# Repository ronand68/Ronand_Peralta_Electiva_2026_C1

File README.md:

Repositorio de la clase Electiva

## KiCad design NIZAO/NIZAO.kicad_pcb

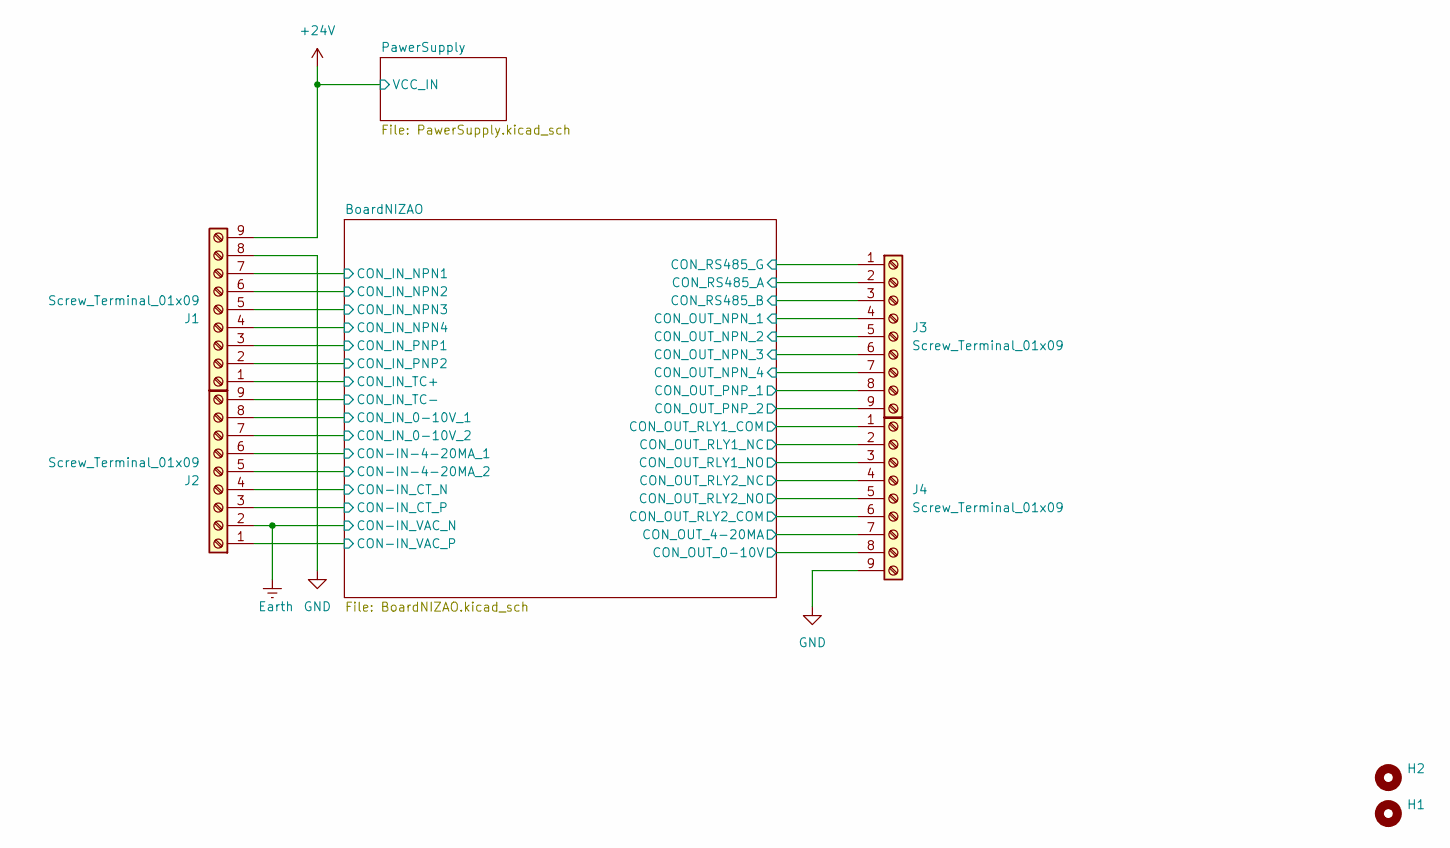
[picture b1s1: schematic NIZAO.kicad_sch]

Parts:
H1, H2: MountingHole; MountingHole_3.2mm_M3
J1, J2, J3, J4: Screw_Terminal_01x09; TerminalBlock_Phoenix_PT-1,5-9-5.0-H_1x09_P5.00mm_Horizontal

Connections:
+24V: J1.9; also elsewhere on the board
/BoardNIZAO/CON-IN-4-20MA_1: J2.6; also elsewhere on the board
/BoardNIZAO/CON-IN-4-20MA_2: J2.5; also elsewhere on the board
/BoardNIZAO/CON-IN_CT_N: J2.4; also elsewhere on the board
/BoardNIZAO/CON-IN_CT_P: J2.3; also elsewhere on the board
/BoardNIZAO/CON-IN_VAC_P: J2.1; also elsewhere on the board
/BoardNIZAO/CON_IN_0-10V_1: J2.8; also elsewhere on the board
/BoardNIZAO/CON_IN_0-10V_2: J2.7; also elsewhere on the board
/BoardNIZAO/CON_IN_NPN1: J1.7; also elsewhere on the board
/BoardNIZAO/CON_IN_NPN2: J1.6; also elsewhere on the board
/BoardNIZAO/CON_IN_NPN3: J1.5; also elsewhere on the board
/BoardNIZAO/CON_IN_NPN4: J1.4; also elsewhere on the board
/BoardNIZAO/CON_IN_PNP1: J1.3; also elsewhere on the board
/BoardNIZAO/CON_IN_PNP2: J1.2; also elsewhere on the board
/BoardNIZAO/CON_IN_TC+: J1.1; also elsewhere on the board
/BoardNIZAO/CON_IN_TC-: J2.9; also elsewhere on the board
/BoardNIZAO/CON_OUT_0-10V: J4.8; also elsewhere on the board
/BoardNIZAO/CON_OUT_4-20MA: J4.7; also elsewhere on the board
/BoardNIZAO/CON_OUT_NPN_1: J3.4; also elsewhere on the board
/BoardNIZAO/CON_OUT_NPN_2: J3.5; also elsewhere on the board
/BoardNIZAO/CON_OUT_NPN_3: J3.6; also elsewhere on the board
/BoardNIZAO/CON_OUT_NPN_4: J3.7; also elsewhere on the board
/BoardNIZAO/CON_OUT_PNP_1: J3.8; also elsewhere on the board
/BoardNIZAO/CON_OUT_PNP_2: J3.9; also elsewhere on the board
/BoardNIZAO/CON_OUT_RLY1_COM: J4.1; also elsewhere on the board
/BoardNIZAO/CON_OUT_RLY1_NC: J4.2; also elsewhere on the board
/BoardNIZAO/CON_OUT_RLY1_NO: J4.3; also elsewhere on the board
/BoardNIZAO/CON_OUT_RLY2_COM: J4.6; also elsewhere on the board
/BoardNIZAO/CON_OUT_RLY2_NC: J4.4; also elsewhere on the board
/BoardNIZAO/CON_OUT_RLY2_NO: J4.5; also elsewhere on the board
/BoardNIZAO/CON_RS485_A: J3.2; also elsewhere on the board
/BoardNIZAO/CON_RS485_B: J3.3; also elsewhere on the board
/BoardNIZAO/CON_RS485_G: J3.1; also elsewhere on the board
Earth: J2.2; also elsewhere on the board
GND: J1.8, J4.9; also elsewhere on the board

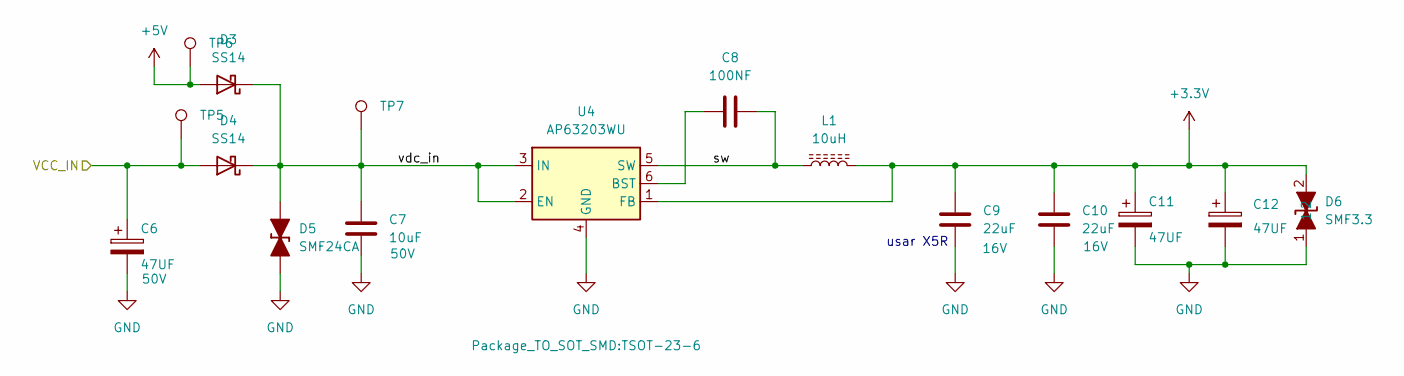
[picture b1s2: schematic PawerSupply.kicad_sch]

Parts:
C6: 47UF; CP_Elec_6.3x7.7; Part Number C2887275; LCSC Part C2887275
C7: 10uF; C_0805_2012Metric; Part Number GRM21BR61H106KE43L; LCSC Part C440198
C8: 100NF; C_0805_2012Metric; Part Number CC0805KRX7R9BB104; LCSC Part C49678
C9, C10: 22uF; C_0805_2012Metric; Part Number CL21A226MOQNNNE; LCSC Part C98190
C11, C12: 47UF; CP_Elec_6.3x7.7; Part Number UUD1C470MCL1GS
D3, D4: SS14; D_SMA
D5: SMF24CA; D_SOD-123F
D6: SMF3.3; SMF3_3CA_C6165153; Manufacturer Part SMF3.3CA; LCSC C6165153
L1: 10uH; L_APV_APH0630; Part Number SL0630-100M; LCSC Part C22463823
TP5, TP6, TP7: TestPoint_Hole1; TestPoint_THTPad_D1.5mm_Drill0.7mm
U4: AP63203WU; TSOT-23-6

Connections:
+3.3V: C9.1, C10.1, C11.1, C12.1, D6.2, L1.2, U4.1 (FB); also elsewhere on the board
+5V: D3.2 (A), TP6.1 (1_1); also elsewhere on the board
+24V: C6.1, D4.2 (A), TP5.1; also elsewhere on the board
/PawerSupply/sw: C8.2, L1.1, U4.5 (SW)
/PawerSupply/vdc_in: C7.1, D3.1 (K), D4.1 (K), D5.2 (A), TP7.1 (1_1), U4.2 (EN), U4.3 (IN)
GND: C6.2, C7.2, C9.2, C10.2, C11.2, C12.2, D5.1 (K), D6.1, U4.4 (GND); also elsewhere on the board
unnamed: C8.1, U4.6 (BST)

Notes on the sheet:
usar X5R

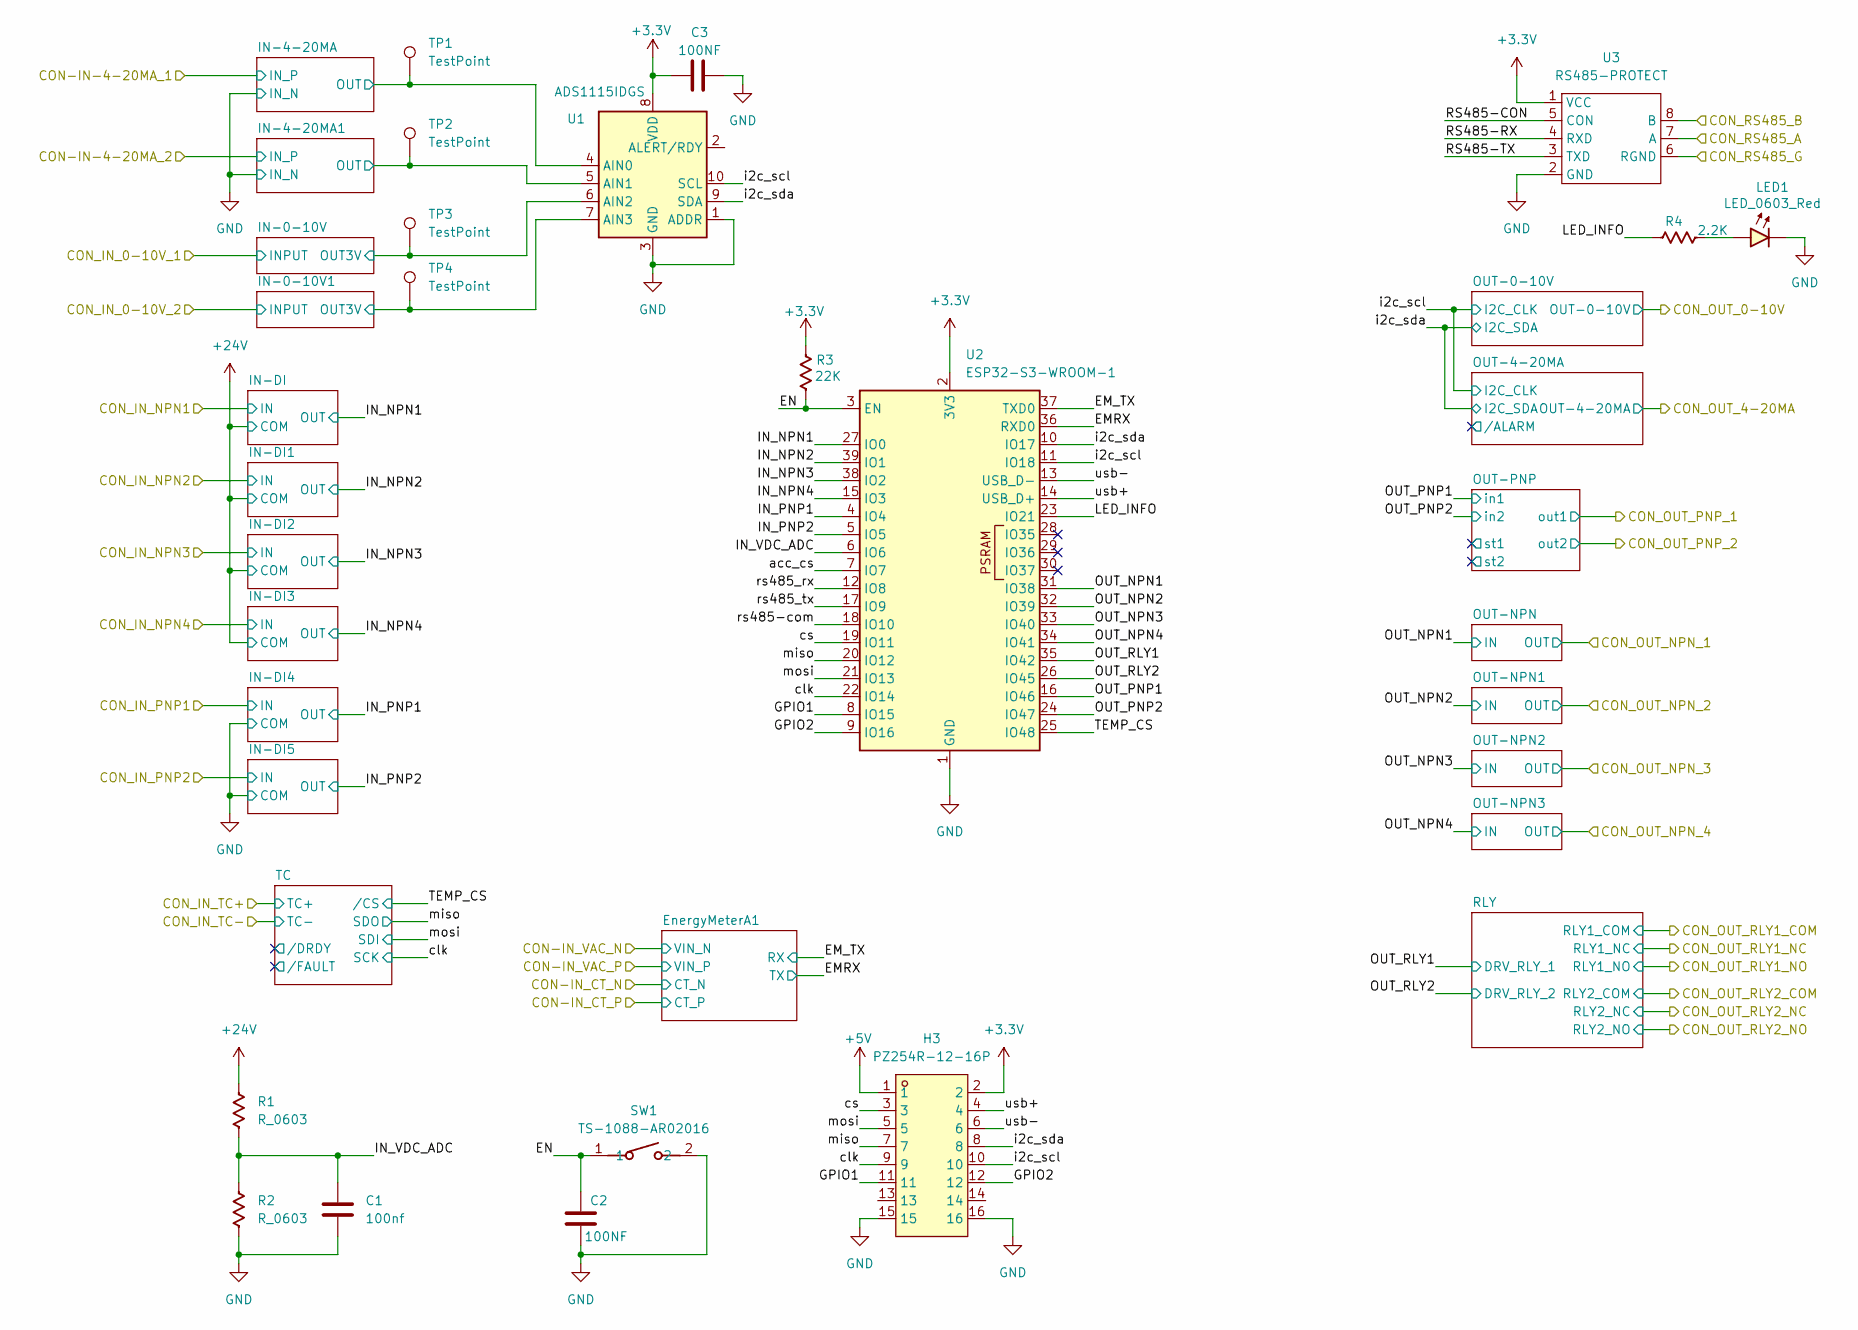
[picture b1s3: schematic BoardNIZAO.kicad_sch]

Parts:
C1: 100nf; C_0603_1608Metric
C2, C3: 100NF; C_0603_1608Metric
H3: PZ254R-12-16P; HDR-TH_16P-P2.54-H-M-R2-C8-S2.54; LCSC Part C492436
LED1: LED_0603_Red; LED_0603_1608Metric
R1, R2: R_0603; R_0603_1608Metric
R3: 22K; R_0603_1608Metric
R4: 2.2K; R_0603_1608Metric
SW1: TS-1088-AR02016; Manufacturer Part TS-1088-AR02016; LCSC C720477
TP1, TP2, TP3, TP4: TestPoint; TestPoint_THTPad_D1.5mm_Drill0.7mm
U1: ADS1115IDGS; TSSOP-10_3x3mm_P0.5mm
U2: ESP32-S3-WROOM-1; ESP32-S3-WROOM-1U
U3: RS485-PROTECT; RS-485-PROTECT; Part Number RS-485-PROTECT

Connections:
+3.3V: C3.1, H3.2, R3.2, U1.8 (VDD), U2.2 (3V3), U3.1 (VCC); also elsewhere on the board
+5V: H3.1; also elsewhere on the board
+24V: R1.1; also elsewhere on the board
/BoardNIZAO/CON_RS485_A: U3.7 (A); also elsewhere on the board
/BoardNIZAO/CON_RS485_B: U3.8 (B); also elsewhere on the board
/BoardNIZAO/CON_RS485_G: U3.6 (RGND); also elsewhere on the board
/BoardNIZAO/EMRX: U2.36 (RXD0); also elsewhere on the board
/BoardNIZAO/EM_TX: U2.37 (TXD0); also elsewhere on the board
/BoardNIZAO/EN: C2.2, R3.1, SW1.1, U2.3 (EN)
/BoardNIZAO/GPIO1: H3.11, U2.8 (IO15)
/BoardNIZAO/GPIO2: H3.12, U2.9 (IO16)
/BoardNIZAO/IN-0-10V1/OUT3V: TP4.1 (1_1), U1.7 (AIN3); also elsewhere on the board
/BoardNIZAO/IN-0-10V/OUT3V: TP3.1 (1_1), U1.6 (AIN2); also elsewhere on the board
/BoardNIZAO/IN-4-20MA1/OUT: TP2.1 (1_1), U1.5 (AIN1); also elsewhere on the board
/BoardNIZAO/IN-4-20MA/OUT: TP1.1 (1_1), U1.4 (AIN0); also elsewhere on the board
/BoardNIZAO/IN_NPN1: U2.27 (IO0); also elsewhere on the board
/BoardNIZAO/IN_NPN2: U2.39 (IO1); also elsewhere on the board
/BoardNIZAO/IN_NPN3: U2.38 (IO2); also elsewhere on the board
/BoardNIZAO/IN_NPN4: U2.15 (IO3); also elsewhere on the board
/BoardNIZAO/IN_PNP1: U2.4 (IO4); also elsewhere on the board
/BoardNIZAO/IN_PNP2: U2.5 (IO5); also elsewhere on the board
/BoardNIZAO/IN_VDC_ADC: C1.1, R1.2, R2.1, U2.6 (IO6)
/BoardNIZAO/LED_INFO: R4.2, U2.23 (IO21)
/BoardNIZAO/OUT_NPN1: U2.31 (IO38); also elsewhere on the board
/BoardNIZAO/OUT_NPN2: U2.32 (IO39); also elsewhere on the board
/BoardNIZAO/OUT_NPN3: U2.33 (IO40); also elsewhere on the board
/BoardNIZAO/OUT_NPN4: U2.34 (IO41); also elsewhere on the board
/BoardNIZAO/OUT_PNP1: U2.16 (IO46); also elsewhere on the board
/BoardNIZAO/OUT_PNP2: U2.24 (IO47); also elsewhere on the board
/BoardNIZAO/OUT_RLY1: U2.35 (IO42); also elsewhere on the board
/BoardNIZAO/OUT_RLY2: U2.26 (IO45); also elsewhere on the board
/BoardNIZAO/RS485-CON: U3.5 (CON)
/BoardNIZAO/RS485-RX: U3.4 (RXD)
/BoardNIZAO/RS485-TX: U3.3 (TXD)
/BoardNIZAO/TEMP_CS: U2.25 (IO48); also elsewhere on the board
/BoardNIZAO/acc_cs: U2.7 (IO7)
/BoardNIZAO/clk: H3.9, U2.22 (IO14); also elsewhere on the board
/BoardNIZAO/cs: H3.3, U2.19 (IO11)
/BoardNIZAO/i2c_scl: H3.10, U1.10 (SCL), U2.11 (IO18); also elsewhere on the board
/BoardNIZAO/i2c_sda: H3.8, U1.9 (SDA), U2.10 (IO17); also elsewhere on the board
/BoardNIZAO/miso: H3.7, U2.20 (IO12); also elsewhere on the board
/BoardNIZAO/mosi: H3.5, U2.21 (IO13); also elsewhere on the board
/BoardNIZAO/rs485-com: U2.18 (IO10)
/BoardNIZAO/rs485_rx: U2.12 (IO8)
/BoardNIZAO/rs485_tx: U2.17 (IO9)
/BoardNIZAO/usb+: H3.4, U2.14 (USB_D+)
/BoardNIZAO/usb-: H3.6, U2.13 (USB_D-)
GND: C1.2, C2.1, C3.2, H3.15, H3.16, LED1.1 (K), R2.2, SW1.2, U1.1 (ADDR), U1.3 (GND), U2.1 (GND), U2.40 (GND), U2.41 (GND), U3.2 (GND); also elsewhere on the board
unnamed: LED1.2 (A), R4.1

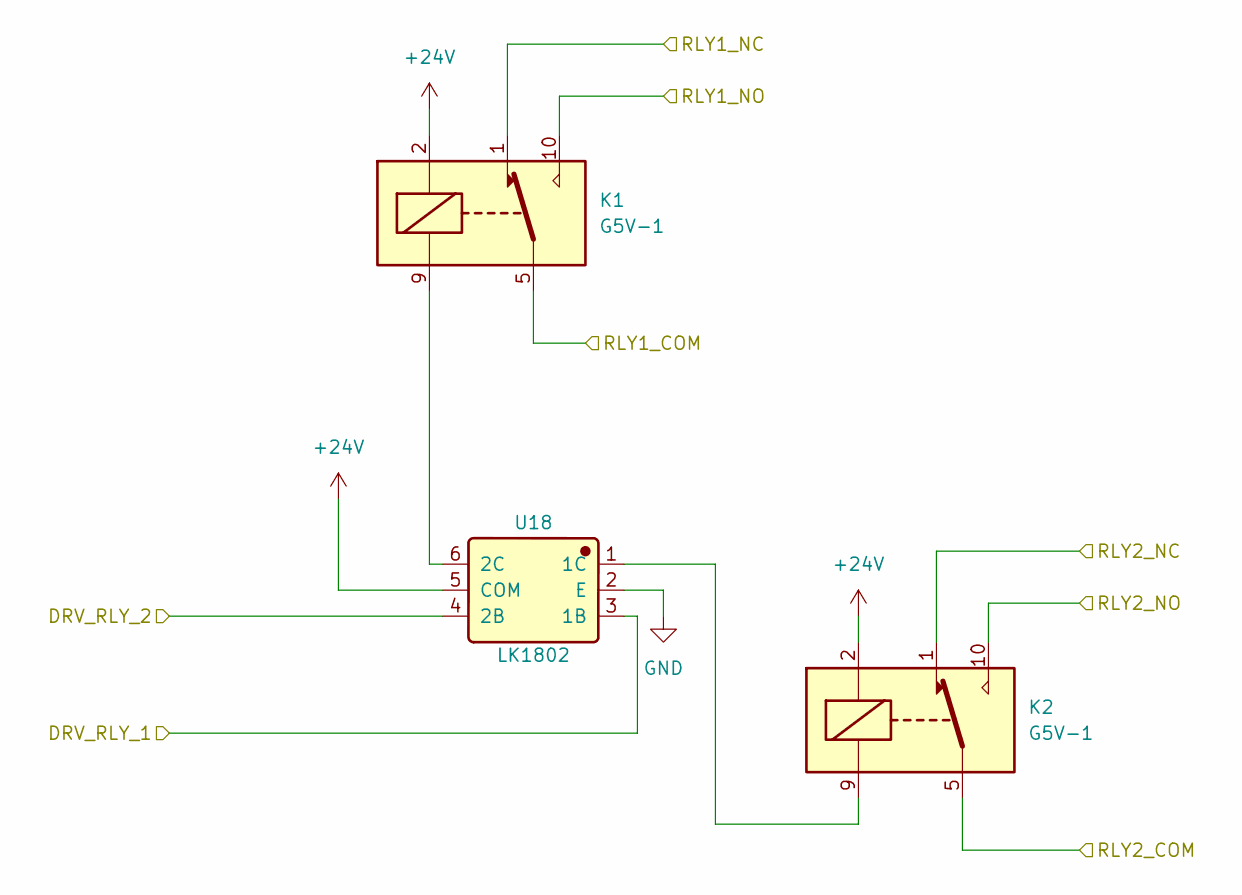
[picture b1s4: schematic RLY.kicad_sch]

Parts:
K1, K2: G5V-1; Relay_SPDT_Omron_G5V-1
U18: LK1802; Manufacturer Part LK1802; LCSC Part C2984831

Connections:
+24V: K1.2, K2.2, U18.5 (COM); also elsewhere on the board
/BoardNIZAO/CON_OUT_RLY1_COM: K1.5, K1.6; also elsewhere on the board
/BoardNIZAO/CON_OUT_RLY1_NC: K1.1; also elsewhere on the board
/BoardNIZAO/CON_OUT_RLY1_NO: K1.10; also elsewhere on the board
/BoardNIZAO/CON_OUT_RLY2_COM: K2.5, K2.6; also elsewhere on the board
/BoardNIZAO/CON_OUT_RLY2_NC: K2.1; also elsewhere on the board
/BoardNIZAO/CON_OUT_RLY2_NO: K2.10; also elsewhere on the board
/BoardNIZAO/OUT_RLY1: U18.3 (1B); also elsewhere on the board
/BoardNIZAO/OUT_RLY2: U18.4 (2B); also elsewhere on the board
GND: U18.2 (E); also elsewhere on the board
unnamed: K2.9, U18.1 (1C)
unnamed: K1.9, U18.6 (2C)

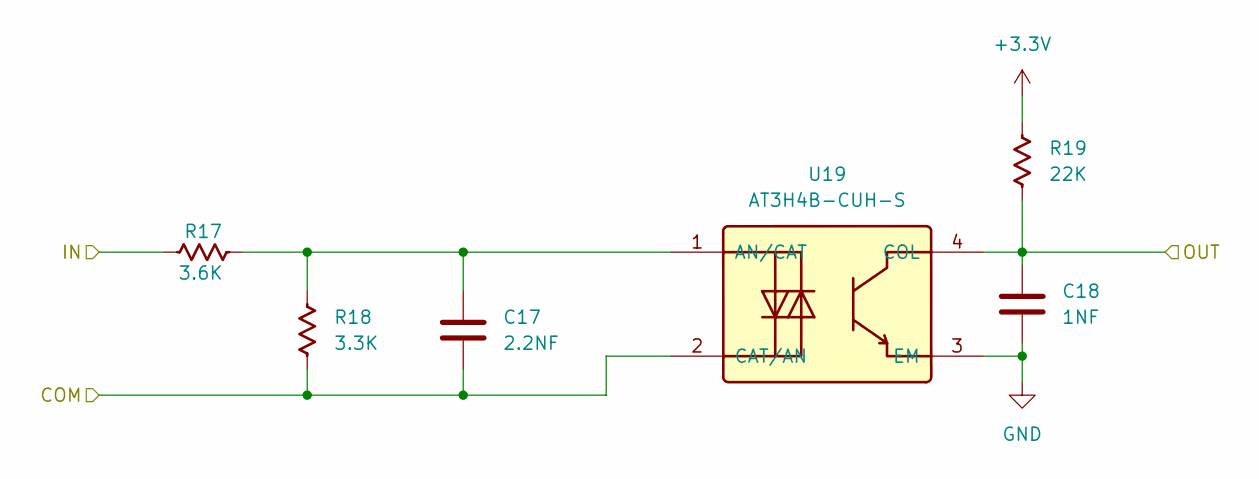
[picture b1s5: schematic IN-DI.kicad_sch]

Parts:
C17: 2.2NF; C_0603_1608Metric
C18: 1NF; C_0603_1608Metric
R17: 3.6K; R_0603_1608Metric
R18: 3.3K; R_0603_1608Metric
R19: 22K; R_0603_1608Metric
U19: AT3H4B-CUH-S; Manufacturer Part AT3H4B-CuH-S; LCSC Part C20612635

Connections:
+3.3V: R19.2; also elsewhere on the board
+24V: C17.2, R18.1, U19.2 (CAT/AN); also elsewhere on the board
/BoardNIZAO/CON_IN_NPN1: R17.1; also elsewhere on the board
/BoardNIZAO/IN_NPN1: C18.1, R19.1, U19.4 (COL); also elsewhere on the board
GND: C18.2, U19.3 (EM); also elsewhere on the board
unnamed: C17.1, R17.2, R18.2, U19.1 (AN/CAT)

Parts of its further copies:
C19, C21, C23, C25, C27: 2.2NF; C_0603_1608Metric
C20, C22, C24, C26, C28: 1NF; C_0603_1608Metric
R20, R23, R26, R29, R32: 3.6K; R_0603_1608Metric
R21, R24, R27, R30, R33: 3.3K; R_0603_1608Metric
R22, R25, R28, R31, R34: 22K; R_0603_1608Metric
U20, U21, U22, U23, U24: AT3H4B-CUH-S; Manufacturer Part AT3H4B-CuH-S; LCSC Part C20612635

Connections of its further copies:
+3.3V: R22.2, R25.2, R28.2, R31.2, R34.2; also elsewhere on the board
+24V: C19.2, C21.2, C23.2, R21.1, R24.1, R27.1, U20.2 (CAT/AN), U21.2 (CAT/AN), U22.2 (CAT/AN); also elsewhere on the board
/BoardNIZAO/CON_IN_NPN2: R20.1; also elsewhere on the board
/BoardNIZAO/CON_IN_NPN3: R23.1; also elsewhere on the board
/BoardNIZAO/CON_IN_NPN4: R26.1; also elsewhere on the board
/BoardNIZAO/CON_IN_PNP1: R29.1; also elsewhere on the board
/BoardNIZAO/CON_IN_PNP2: R32.1; also elsewhere on the board
/BoardNIZAO/IN_NPN2: C20.1, R22.1, U20.4 (COL); also elsewhere on the board
/BoardNIZAO/IN_NPN3: C22.1, R25.1, U21.4 (COL); also elsewhere on the board
/BoardNIZAO/IN_NPN4: C24.1, R28.1, U22.4 (COL); also elsewhere on the board
/BoardNIZAO/IN_PNP1: C26.1, R31.1, U23.4 (COL); also elsewhere on the board
/BoardNIZAO/IN_PNP2: C28.1, R34.1, U24.4 (COL); also elsewhere on the board
GND: C20.2, C22.2, C24.2, C25.2, C26.2, C27.2, C28.2, R30.1, R33.1, U20.3 (EM), U21.3 (EM), U22.3 (EM), U23.2 (CAT/AN), U23.3 (EM), U24.2 (CAT/AN), U24.3 (EM); also elsewhere on the board
unnamed: C19.1, R20.2, R21.2, U20.1 (AN/CAT)
unnamed: C21.1, R23.2, R24.2, U21.1 (AN/CAT)
unnamed: C23.1, R26.2, R27.2, U22.1 (AN/CAT)
unnamed: C25.1, R29.2, R30.2, U23.1 (AN/CAT)
unnamed: C27.1, R32.2, R33.2, U24.1 (AN/CAT)

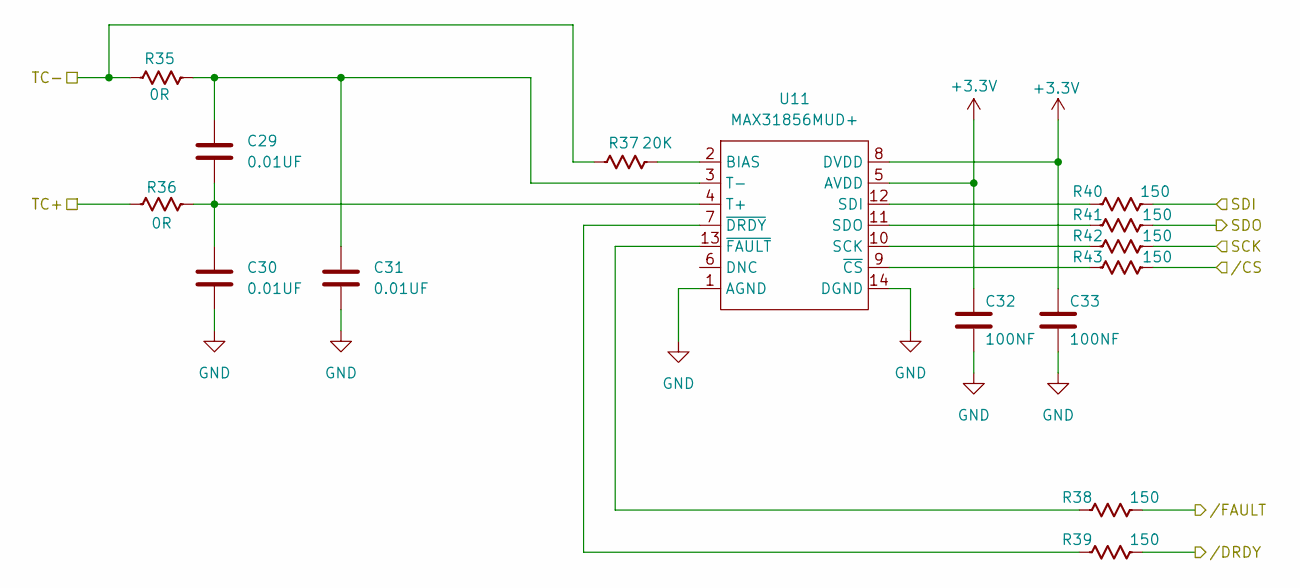
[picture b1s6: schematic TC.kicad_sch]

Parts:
C29, C30, C31: 0.01UF; C_0603_1608Metric
C32, C33: 100NF; C_0603_1608Metric
R35, R36: 0R; R_0603_1608Metric
R37: 20K; R_0603_1608Metric
R38, R39, R40, R41, R42, R43: 150; R_0603_1608Metric
U11: MAX31856MUD+; MAX31856MUD; LCSC Part C116632

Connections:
+3.3V: C32.1, C33.1, U11.5 (AVDD), U11.8 (DVDD); also elsewhere on the board
/BoardNIZAO/CON_IN_TC+: R36.1; also elsewhere on the board
/BoardNIZAO/CON_IN_TC-: R35.1, R37.1; also elsewhere on the board
/BoardNIZAO/TC//DRDY: R39.2
/BoardNIZAO/TC//FAULT: R38.2
/BoardNIZAO/TEMP_CS: R43.2; also elsewhere on the board
/BoardNIZAO/clk: R42.2; also elsewhere on the board
/BoardNIZAO/miso: R41.2; also elsewhere on the board
/BoardNIZAO/mosi: R40.2; also elsewhere on the board
GND: C30.2, C31.2, C32.2, C33.2, U11.1 (AGND), U11.14 (DGND); also elsewhere on the board
unnamed: R37.2, U11.2 (BIAS)
unnamed: R42.1, U11.10 (SCK)
unnamed: R40.1, U11.12 (SDI)
unnamed: R41.1, U11.11 (SDO)
unnamed: C29.2, C30.1, R36.2, U11.4 (T+)
unnamed: C29.1, C31.1, R35.2, U11.3 (T-)
unnamed: R43.1, U11.9 (~CS)
unnamed: R39.1, U11.7 (~DRDY)
unnamed: R38.1, U11.13 (~FAULT)

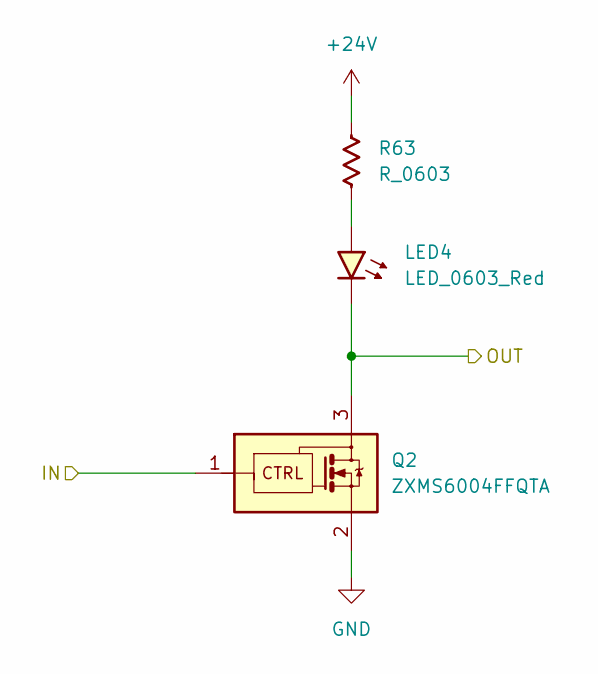
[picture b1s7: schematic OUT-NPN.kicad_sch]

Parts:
LED4: LED_0603_Red; LED_0603_1608Metric
Q2: ZXMS6004FFQTA; SOT-23-3; Part Number ZXMS6004FFQTA
R63: R_0603; R_0603_1608Metric

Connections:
+24V: R63.1; also elsewhere on the board
/BoardNIZAO/CON_OUT_NPN_1: LED4.1 (K), Q2.3 (D); also elsewhere on the board
/BoardNIZAO/OUT_NPN1: Q2.1 (IN); also elsewhere on the board
GND: Q2.2 (OUT); also elsewhere on the board
unnamed: LED4.2 (A), R63.2

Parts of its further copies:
LED5, LED6, LED7: LED_0603_Red; LED_0603_1608Metric
Q3, Q4, Q5: ZXMS6004FFQTA; SOT-23-3; Part Number ZXMS6004FFQTA
R64, R65, R66: R_0603; R_0603_1608Metric

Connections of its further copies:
+24V: R64.1, R65.1, R66.1; also elsewhere on the board
/BoardNIZAO/CON_OUT_NPN_2: LED5.1 (K), Q3.3 (D); also elsewhere on the board
/BoardNIZAO/CON_OUT_NPN_3: LED6.1 (K), Q4.3 (D); also elsewhere on the board
/BoardNIZAO/CON_OUT_NPN_4: LED7.1 (K), Q5.3 (D); also elsewhere on the board
/BoardNIZAO/OUT_NPN2: Q3.1 (IN); also elsewhere on the board
/BoardNIZAO/OUT_NPN3: Q4.1 (IN); also elsewhere on the board
/BoardNIZAO/OUT_NPN4: Q5.1 (IN); also elsewhere on the board
GND: Q3.2 (OUT), Q4.2 (OUT), Q5.2 (OUT); also elsewhere on the board
unnamed: LED5.2 (A), R64.2
unnamed: LED6.2 (A), R65.2
unnamed: LED7.2 (A), R66.2

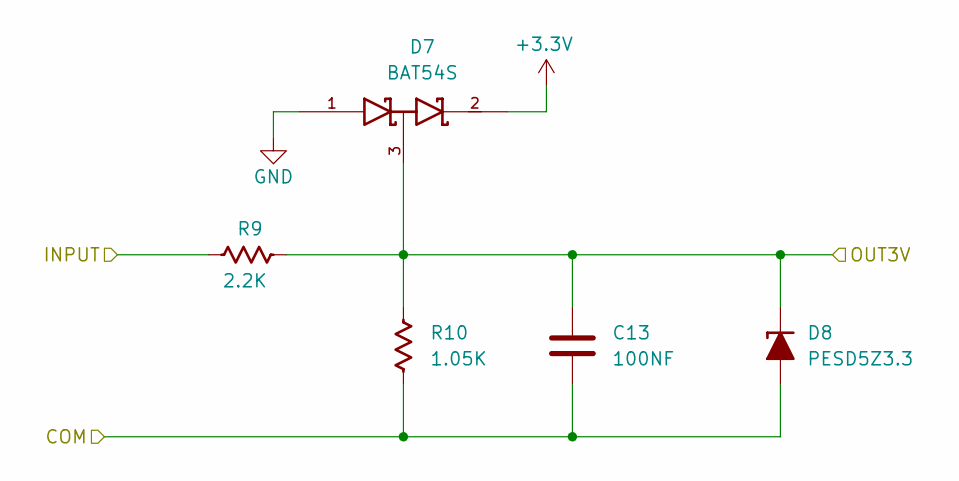
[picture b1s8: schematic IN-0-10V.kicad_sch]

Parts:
C13: 100NF; C_0603_1608Metric
D7: BAT54S; BAT54S-7-F; Part Number BAT54S-7-F; JLCPCB ID C83574
D8: PESD5Z3.3; D_SOD-523
R9: 2.2K; R_0603_1608Metric
R10: 1.05K; R_0603_1608Metric

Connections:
+3.3V: D7.2 (cathode); also elsewhere on the board
/BoardNIZAO/CON_IN_0-10V_1: R9.1; also elsewhere on the board
/BoardNIZAO/IN-0-10V/COM: C13.2, D8.2 (A), R10.2
/BoardNIZAO/IN-0-10V/OUT3V: C13.1, D7.3 (AK), D8.1 (K), R9.2, R10.1; also elsewhere on the board
GND: D7.1 (Anode); also elsewhere on the board

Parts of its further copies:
C16: 100NF; C_0603_1608Metric
D11: BAT54S; BAT54S-7-F; Part Number BAT54S-7-F; JLCPCB ID C83574
D12: PESD5Z3.3; D_SOD-523
R15: 2.2K; R_0603_1608Metric
R16: 1.05K; R_0603_1608Metric

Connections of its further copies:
+3.3V: D11.2 (cathode); also elsewhere on the board
/BoardNIZAO/CON_IN_0-10V_2: R15.1; also elsewhere on the board
/BoardNIZAO/IN-0-10V1/COM: C16.2, D12.2 (A), R16.2
/BoardNIZAO/IN-0-10V1/OUT3V: C16.1, D11.3 (AK), D12.1 (K), R15.2, R16.1; also elsewhere on the board
GND: D11.1 (Anode); also elsewhere on the board

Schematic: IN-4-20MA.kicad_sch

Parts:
C4: 100NF; C_0603_1608Metric
C5: 47PF; C_0603_1608Metric
D1: 1N5819HW-7-F; Manufacturer Part 1N5819HW-7-F; LCSC Part C82544
D2: PESD5Z3.3; D_SOD-523
R5: 49.9R; R_0603_1608Metric
R6: 120R; R_0603_1608Metric
R7: 47K; R_0603_1608Metric
R8: 100K; R_0603_1608Metric

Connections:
/BoardNIZAO/CON-IN-4-20MA_1: R5.2; also elsewhere on the board
/BoardNIZAO/IN-4-20MA/OUT: C5.1, D2.1 (K), R8.1; also elsewhere on the board
GND: C4.2, C5.2, D1.2 (A), D2.2 (A), R6.1; also elsewhere on the board
unnamed: C4.1, R7.1, R8.2
unnamed: D1.1 (K), R5.1, R6.2, R7.2

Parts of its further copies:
C14: 100NF; C_0603_1608Metric
C15: 47PF; C_0603_1608Metric
D9: 1N5819HW-7-F; Manufacturer Part 1N5819HW-7-F; LCSC Part C82544
D10: PESD5Z3.3; D_SOD-523
R11: 49.9R; R_0603_1608Metric
R12: 120R; R_0603_1608Metric
R13: 47K; R_0603_1608Metric
R14: 100K; R_0603_1608Metric

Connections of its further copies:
/BoardNIZAO/CON-IN-4-20MA_2: R11.2; also elsewhere on the board
/BoardNIZAO/IN-4-20MA1/OUT: C15.1, D10.1 (K), R14.1; also elsewhere on the board
GND: C14.2, C15.2, D9.2 (A), D10.2 (A), R12.1; also elsewhere on the board
unnamed: C14.1, R13.1, R14.2
unnamed: D9.1 (K), R11.1, R12.2, R13.2

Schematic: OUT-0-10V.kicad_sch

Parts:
C40, C41: C_0603; C_0603_1608Metric
C42: 100nF; C_0603_1608Metric
D13: SD12_SOD323; D_SOD-323
U15: GP8211S-TC50-EW; Manufacturer Part GP8211S-TC50-EW; LCSC Part C3152008

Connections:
+24V: C41.1, U15.4 (VCC); also elsewhere on the board
/BoardNIZAO/CON_OUT_0-10V: C42.1, D13.2 (A2), U15.6 (VOUT); also elsewhere on the board
/BoardNIZAO/i2c_scl: U15.1 (SCLK); also elsewhere on the board
/BoardNIZAO/i2c_sda: U15.2 (SDA); also elsewhere on the board
GND: C40.2, C41.2, C42.2, D13.1 (A1), U15.5 (GND), U15.9 (EP); also elsewhere on the board
unnamed: C40.1, U15.8 (V5V)

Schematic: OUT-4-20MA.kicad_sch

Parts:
C43, C44: C_0603; C_0603_1608Metric
C45: 1uF; C_0603_1608Metric
D14: SMAJ12A; D_SMA
D15: SMBJ28A; D_SMB
D16: DSK120_C22466355; D_SOD-123; LCSC Part C22466355
Q1: NCE60P04R; Manufacturer Part NCE60P04R; LCSC Part C502855
R58: R_0603; R_0603_1608Metric
R59: 470K; R_0603_1608Metric
R60: 15R; R_0805_2012Metric
U16: GP8302-TC50-EW; Manufacturer Part GP8302-TC50-EW; LCSC Part C2856295

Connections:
+24V: C44.1, D14.1 (A1), U16.4 (VCC); also elsewhere on the board
/BoardNIZAO/CON_OUT_4-20MA: D16.1 (C); also elsewhere on the board
/BoardNIZAO/OUT-4-20MA//ALARM: U16.3 (ALARM#)
/BoardNIZAO/i2c_scl: U16.1 (SLCK); also elsewhere on the board
/BoardNIZAO/i2c_sda: U16.2 (SDA); also elsewhere on the board
GND: C43.2, C44.2, C45.2, D15.2 (A), R58.2, R59.2, U16.5 (GND), U16.9 (EP); also elsewhere on the board
unnamed: C45.1, D14.2 (A2), Q1.1 (G), R59.1
unnamed: D15.1 (K), Q1.2 (D), Q1.4 (D), R60.1
unnamed: D16.2 (A), R60.2
unnamed: Q1.3 (S), U16.7 (IOUT)
unnamed: R58.1, U16.6 (SET)
unnamed: C43.1, U16.8 (V5V)

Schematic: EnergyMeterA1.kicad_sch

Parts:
C34, C35: 33NF; C_0603_1608Metric
C36: 68NF; C_0603_1608Metric
C37, C38, C39: 100NF; C_0603_1608Metric
R44, R47, R50, R51, R52: 390K; R_0603_1608Metric
R45, R46: 0.51; R_0805_2012Metric
R48, R49: 1K; R_0603_1608Metric
R53: 510; R_0603_1608Metric
R54, R55, R56, R57: 4.7K; R_0603_1608Metric
TP8, TP9, TP10, TP11: TestPoint_Hole1; TestPoint_THTPad_D1.5mm_Drill0.7mm
U12: BL0942; LCSC Part C2837510
U13: B0303S-1WR3_C7465185; Manufacturer Part B0303S-1WR3; LCSC Part C7465185
U14: ISO7021DR; LCSC Part C2867957

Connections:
+3.3V: C39.2, R56.2, R57.2, U13.2 (+Vin), U14.1 (VCC1); also elsewhere on the board
/BoardNIZAO/CON-IN_CT_N: R46.2, R49.1; also elsewhere on the board
/BoardNIZAO/CON-IN_CT_P: R45.1, R48.1; also elsewhere on the board
/BoardNIZAO/CON-IN_VAC_P: R44.1; also elsewhere on the board
/BoardNIZAO/EMRX: R57.1, U14.2 (OUTA); also elsewhere on the board
/BoardNIZAO/EM_TX: R56.1, U14.3 (INB); also elsewhere on the board
Earth: C34.1, C35.2, C36.1, C37.1, C38.1, R45.2, R46.1, R53.1, U12.5 (GND), U12.7 (SEL), U13.3 (-Vout), U14.5 (GND2); also elsewhere on the board
GND: C39.1, U13.1 (-Vin), U14.4 (GND1); also elsewhere on the board
unnamed: R44.2, R47.1
unnamed: R47.2, R50.1
unnamed: R50.2, R51.1
unnamed: R51.2, R52.1
unnamed: C35.1, R49.2, TP9.1 (1_1), U12.3 (IN)
unnamed: C34.2, R48.2, TP10.1 (1_1), U12.2 (IP)
unnamed: R54.1, U12.9 (RX/SDI), U14.6 (OUTB)
unnamed: R55.1, U12.10 (TX/SDO), U14.7 (INA)
unnamed: C36.2, R52.2, R53.2, TP8.1 (1_1), U12.4 (VP)
VCC: C37.2, C38.2, R54.2, R55.2, TP11.1 (1_1), U12.1 (VDD), U12.8 (SCLK_BPS), U13.4 (+Vout), U14.8 (VCC2)

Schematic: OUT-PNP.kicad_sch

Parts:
LED2, LED3: LED_0603_Red; LED_0603_1608Metric
R61, R62: R_0603; R_0603_1608Metric
U17: BTS723GWXUMA1; LCSC Part C67625

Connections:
+3.3V: U17.11 (SPU); also elsewhere on the board
+24V: U17.1 (VBB), U17.7 (VBB), U17.8 (VBB), U17.14 (VBB); also elsewhere on the board
/BoardNIZAO/CON_OUT_PNP_1: R62.1, U17.9 (OUT2), U17.10 (OUT2); also elsewhere on the board
/BoardNIZAO/CON_OUT_PNP_2: R61.1, U17.12 (OUT1), U17.13 (OUT1); also elsewhere on the board
/BoardNIZAO/OUT-PNP/st1: U17.3 (ST1)
/BoardNIZAO/OUT-PNP/st2: U17.5 (ST2)
/BoardNIZAO/OUT_PNP1: U17.2 (IN1); also elsewhere on the board
/BoardNIZAO/OUT_PNP2: U17.6 (IN2); also elsewhere on the board
GND: LED2.1 (K), LED3.1 (K), U17.4 (GND); also elsewhere on the board
unnamed: LED2.2 (A), R61.2
unnamed: LED3.2 (A), R62.2

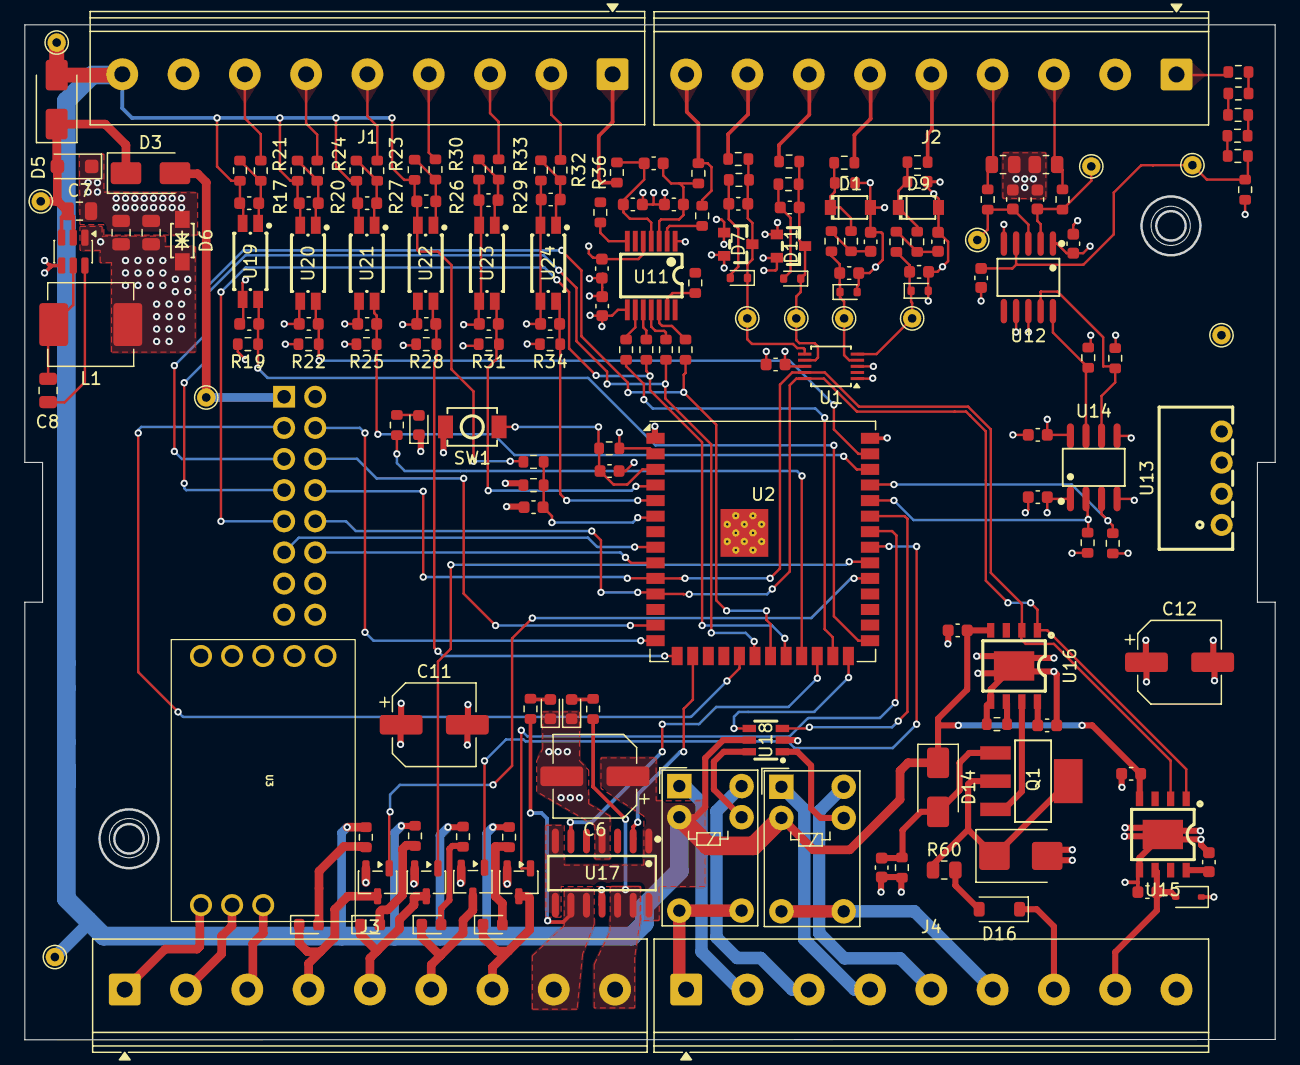
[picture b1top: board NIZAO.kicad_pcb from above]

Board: 4 copper layers, 102.0 x 82.8 mm, 180 parts (0 on the bottom side), 121 nets.

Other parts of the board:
TP5#2: TestPoint_Hole1; TestPoint_THTPad_D1.5mm_Drill0.7mm

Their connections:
+24V: TP5#2.1 (1_1); also elsewhere on the board

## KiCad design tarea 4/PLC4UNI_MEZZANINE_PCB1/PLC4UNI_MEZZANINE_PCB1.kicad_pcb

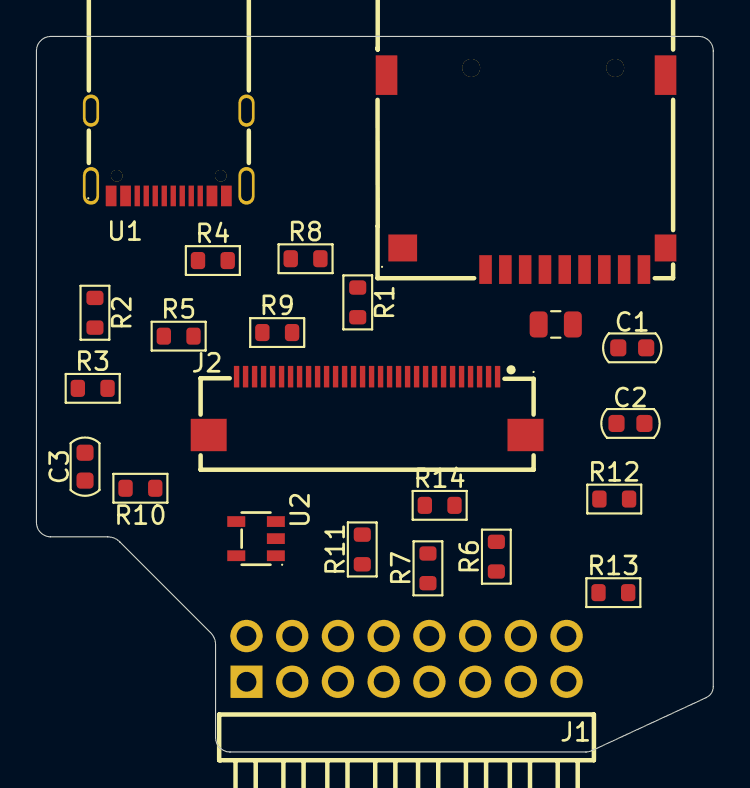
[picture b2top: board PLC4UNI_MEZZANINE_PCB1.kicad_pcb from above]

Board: 2 copper layers, 37.6 x 39.8 mm, 23 parts (0 on the bottom side), 26 nets, no tracks yet.

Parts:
C1: 47uF; C_0603_1608Metric
C2: 100nF; C_0603_1608Metric
C3: 10uF; C_0603_1608Metric
Card1: TF-115; TF-SMD_TF-115
J1: PZ254R-12-16P; HDR-TH_16P-P2.54-H-M-R2-C8-S2.54
J2: FPC-05FB-30PH20; FPC-SMD_30P-P0.50_FPC-05FB-30PH20
L1: 600 Ohm; C_0805_2012Metric
R1, R2: 5.1k; R_0603_1608Metric
R3, R5: 2.2K; R_0603_1608Metric
R4, R8, R9, R12, R13, R14: 10K; R_0603_1608Metric
R6: 10R; R_0603_1608Metric
R7: 220R; R_0603_1608Metric
R10: 6.8K; R_0603_1608Metric
R11: 300; R_0603_1608Metric
U1: MC-121-L119; USB-C-SMD_HANBO_MC-121-L119
U2: MT9700-N; SOT-23-5_L2.9-W1.6-P0.95-LS2.9-BL

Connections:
+3.3V: C3.1, J1.2, L1.2, R3.1, R4.1, R5.1, R8.1, R9.1, R12.1, R13.1, R14.1, U2.5 (VIN)
+5V: J1.1, U1.A4B9 (VBUS), U1.B4A9 (VBUS)
/I2C_SCK: J1.10, J2.26
/I2C_SDA: J1.8, J2.27
/IM2: J2.3, R12.2, R13.2
/LCD_CS: J1.13, J2.6
/LCD_EN: J1.12, U2.4 (EN)
/LED+: J2.20, R11.2
/RESET: J1.11, J2.5, J2.29, R14.2
/SD_CS: Card1.2 (CD/DAT3), J1.3, R9.2
/SPI_CLK: J1.9, J2.7, R6.1
/SPI_MISO: J1.7, J2.19, R5.2, R7.1
/SPI_MOSI: Card1.3 (CMD), J1.5, J2.10, R3.2
/TP_INT: J1.14, J2.28
/USB+: J1.4, U1.A6 (DP1), U1.B6 (DP2)
/USB-: J1.6, U1.A7 (DN1), U1.B7 (DN2)
GND: C1.2, C2.2, C3.2, Card1.6 (VSS), Card1.10 (SHELL), Card1.11 (SHELL), Card1.12 (SHELL), Card1.13 (SHELL), J1.15, J1.16, J2.1, J2.21, J2.22, J2.23, J2.24, J2.30, J2.31, J2.32, R1.2, R2.2, R10.2, U1.13 (EH), U1.A1B12 (GND), U1.B1A12 (GND), U2.2 (GND)
unnamed: Card1.5 (CLK), R6.2
unnamed: Card1.7 (DAT0), R7.2
unnamed: Card1.8 (DAT1), R4.2
unnamed: Card1.1 (DAT2), R8.2
unnamed: C1.1, C2.1, Card1.4 (VDD), L1.1
unnamed: R1.1, U1.A5 (CC1)
unnamed: R2.1, U1.B5 (CC2)
unnamed: R10.1, U2.3 (SET)
VDD: J2.2, J2.25, R11.1, U2.1 (VOUT)

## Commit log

2026-01-16 commit inicial
2026-01-16 cambio de nombre del archivo1.txt
2026-01-16 Devolviendo el nombre del archivo
2026-01-17 Elimenar archivo1.txt
2026-01-17 Eliminar Archivo2.txt
2026-02-04 Agrego tarea 1
2026-02-04 Subo tareas 1, 2 y 3
2026-02-05 Actualizo tarea 3
2026-03-02 Modificado tarea 2, tarea 3, y el documento de la tarea 1
2026-03-02 cambiando nombre del case de plastico
2026-03-10 Actualizan y creando tarea 4
2026-03-12 actualizado
2026-03-12 actualizacion
2026-04-01 Actualiza el mezzanine, eliminar assembly de prueba y actualizar essembly
2026-04-02 actualizar Mezzanine y Assembly
2026-04-04 Colocandos los 3d de los componetes en la placa NIZAO
2026-04-04 atualizando
2026-04-16 ACtualizandos las medidad del case de plastico y NIZAO
2026-04-20 Agregado tarea 5
2026-04-21 Actualizando firmware
